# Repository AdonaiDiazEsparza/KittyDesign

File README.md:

# Kitty Design

---

## Description
This repository contains the design files for Kitty Design, a small PCB project to create a light sequence. The board is powered by an inexpensive yet powerful PY32f002 microcontroller from the PUYA series. These low-power chips are efficient enough to be powered by a single coin cell battery (CR2032) for an extended period. This project was created for fun and as a practical exercise in using KiCad 9.

---

## Components
1x CH32V003JxMx

1x 100nF Capacitor

1x CR2032 Battery Holder

5x LEDs

5x 330 Ohm Resistors

1x Switch

---

## Design Images

## Author
Adonai Diaz

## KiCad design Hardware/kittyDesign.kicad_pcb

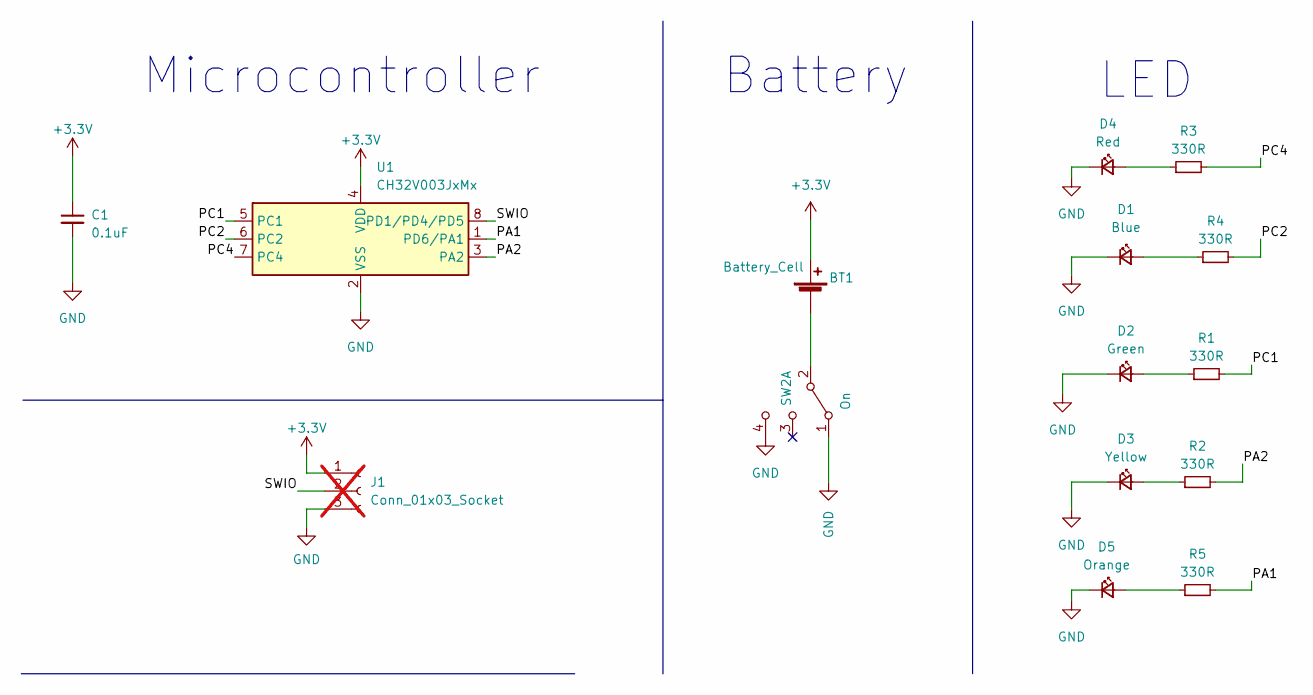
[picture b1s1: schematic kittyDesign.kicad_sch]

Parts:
BT1: Battery_Cell; BAT-HLD-001; LCSC# C964833
C1: 0.1uF; C_0805_2012Metric; LCSC# C235731
D1: Blue; LED_0805_2012Metric; LCSC# C205441
D2: Green; LED_0805_2012Metric; LCSC# C965815
D3: Yellow; LED_0805_2012Metric; LCSC# C84261
D4: Red; LED_0805_2012Metric; LCSC# C965812
D5: Orange; LED_0805_2012Metric; LCSC# C434437
J1: Conn_01x03_Socket; PinHeader_1x03_P2.54mm_Vertical; not fitted
R1, R2, R3, R4, R5: 330R; R_0805_2012Metric; LCSC# C119075
SW2: On; MSK12C02; LCSC# C431540
U1: CH32V003JxMx; JEITA_SOIC-8_3.9x4.9mm_P1.27mm

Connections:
+3.3V: BT1.2 (+), C1.1, J1.1, U1.4 (VDD)
/PA1: R5.2, U1.1 (PD6/PA1)
/PA2: R2.2, U1.3 (PA2)
/PC1: R1.2, U1.5 (PC1)
/PC2: R4.2, U1.6 (PC2)
/PC4: R3.2, U1.7 (PC4)
/SWIO: J1.2, U1.8 (PD1/PD4/PD5)
GND: C1.2, D1.1 (K), D2.1 (K), D3.1 (K), D4.1 (K), D5.1 (K), J1.3, SW2.1 (A), SW2.4 (C), U1.2 (VSS)
unnamed: BT1.1 (-), SW2.2 (B)
unnamed: D1.2 (A), R4.1
unnamed: D2.2 (A), R1.1
unnamed: D3.2 (A), R2.1
unnamed: D4.2 (A), R3.1
unnamed: D5.2 (A), R5.1

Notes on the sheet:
LED
Battery
Microcontroller

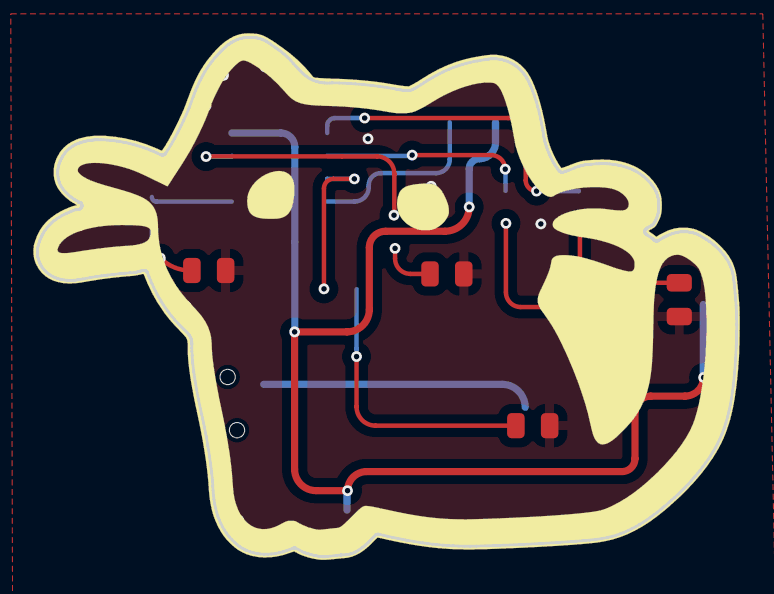
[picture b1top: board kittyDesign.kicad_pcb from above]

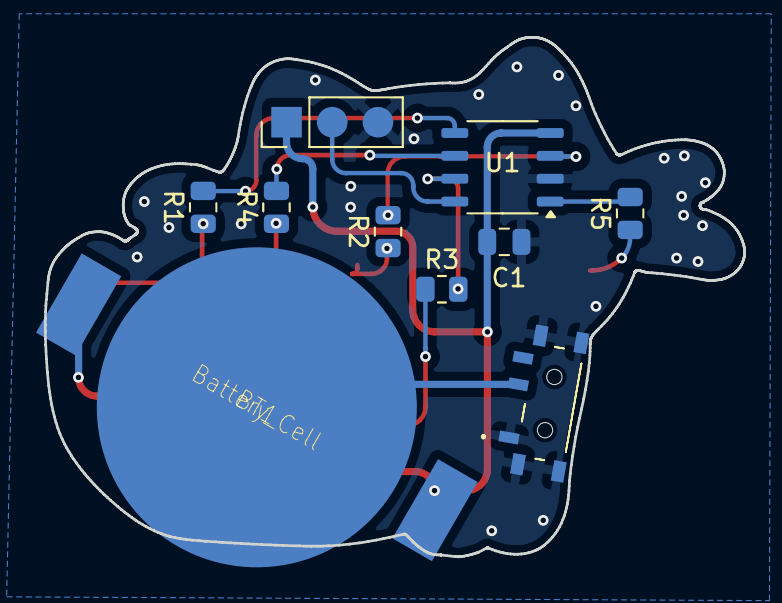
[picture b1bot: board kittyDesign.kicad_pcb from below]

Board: 2 copper layers, 38.9 x 28.9 mm, 16 parts (10 on the bottom side), 14 nets.

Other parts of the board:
Ref**: Val**; drawing

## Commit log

2025-08-06 feat: add gitignore
2025-08-06 feat: add resources
2025-08-08 featÑ add routes
2025-08-08 feat: add images
2025-08-08 feat: create readme
2025-08-08 feat: test image
2025-08-08 fix: images
2025-08-11 refactor: change MCU for a ch32v00x
2025-08-11 feat: update readme
2025-08-12 feat: update project
